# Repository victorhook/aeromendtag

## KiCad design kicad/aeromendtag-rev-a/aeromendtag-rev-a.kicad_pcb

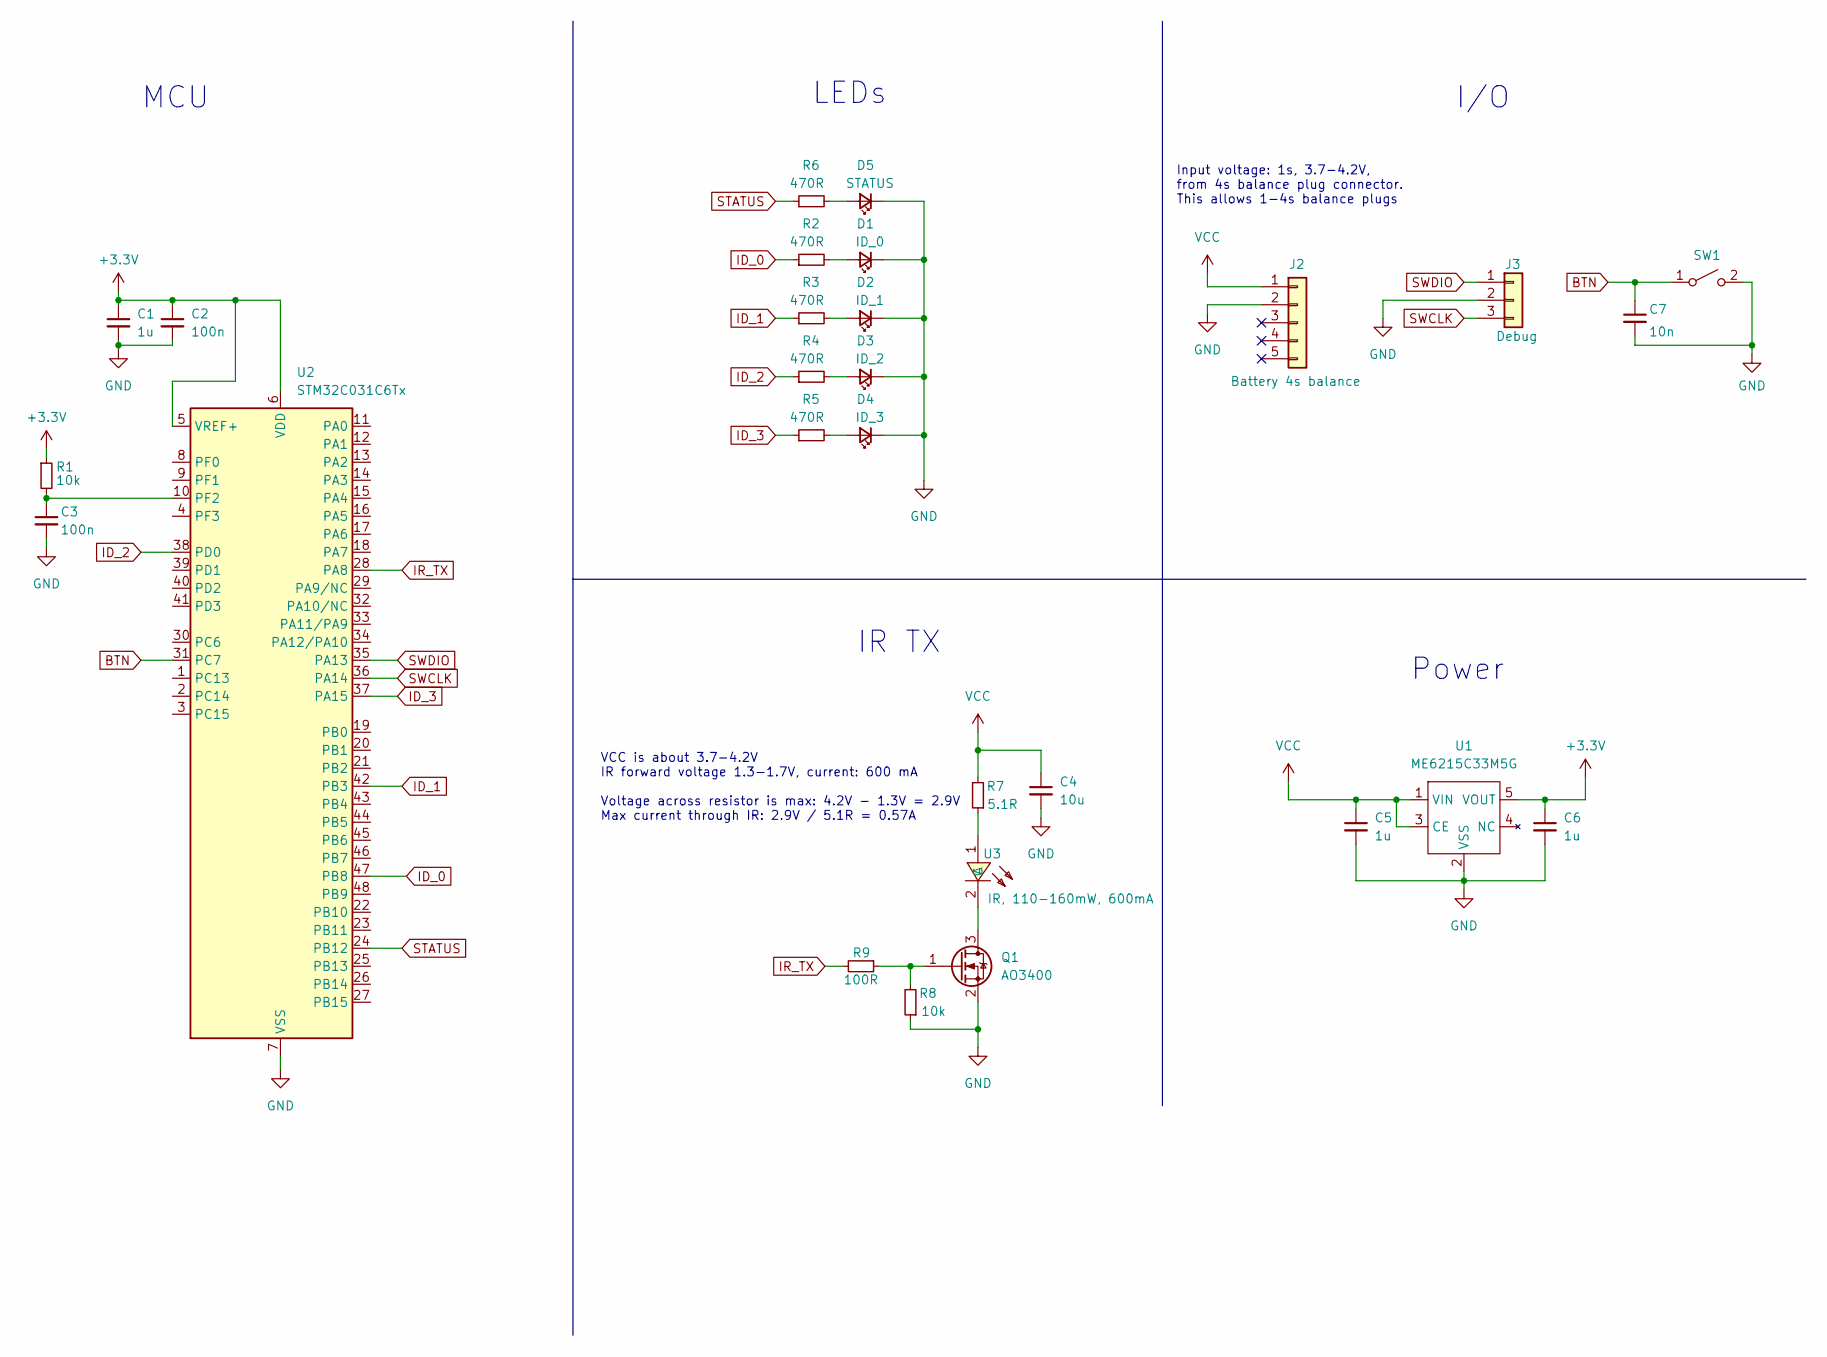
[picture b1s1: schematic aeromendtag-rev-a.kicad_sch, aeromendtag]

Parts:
C1, C5, C6: 1u; C_0402_1005Metric
C2, C3: 100n; C_0402_1005Metric
C4: 10u; C_0603_1608Metric
C7: 10n; C_0402_1005Metric
D1: ID_0; LED_0603_1608Metric
D2: ID_1; LED_0603_1608Metric
D3: ID_2; LED_0603_1608Metric
D4: ID_3; LED_0603_1608Metric
D5: STATUS; LED_0603_1608Metric
J2: Battery 4s balance; PinSocket_1x05_P2.54mm_Vertical
J3: Debug; PinHeader_1x03_P1.27mm_Vertical
Q1: AO3400; SOT-23; MPN C122850
R1, R8: 10k; R_0402_1005Metric
R2, R3, R4, R5, R6: 470R; R_0402_1005Metric
R7: 5.1R; R_2512_6332Metric; MPN C105134
R9: 100R; R_0402_1005Metric
SW1: SW_SPST; SW-SMD_L4.0-W2.9-LS5.0
U1: ME6215C33M5G; SOT-23-5; MPN C84119
U2: STM32C031C6Tx; LQFP-48_7x7mm_P0.5mm; MPN C5456218
U3: IR, 110-160mW, 600mA; SENSOR-SMD_L3.9-W3.9-FD; MPN C5205232; LCSC Part C5205232

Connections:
+3.3V: C1.1, C2.1, C6.1, R1.1, U1.5 (VOUT), U2.5 (VREF+), U2.6 (VDD)
BTN: C7.1, SW1.1 (A), U2.31 (PC7)
GND: C1.2, C2.2, C3.2, C4.2, C5.2, C6.2, C7.2, D1.1 (K), D2.1 (K), D3.1 (K), D4.1 (K), D5.1 (K), J2.2, J3.2, Q1.2 (S), R8.1, SW1.2 (B), U1.2 (VSS), U2.7 (VSS)
ID_0: R2.1, U2.47 (PB8)
ID_1: R3.1, U2.42 (PB3)
ID_2: R4.1, U2.38 (PD0)
ID_3: R5.1, U2.37 (PA15)
IR_TX: R9.2, U2.28 (PA8)
unnamed: D1.2 (A), R2.2
unnamed: D2.2 (A), R3.2
unnamed: D3.2 (A), R4.2
unnamed: D4.2 (A), R5.2
unnamed: D5.2 (A), R6.2
unnamed: Q1.3 (D), U3.2 (C)
unnamed: Q1.1 (G), R8.2, R9.1
unnamed: C3.1, R1.2, U2.10 (PF2)
unnamed: R7.1, U3.1 (A)
STATUS: R6.1, U2.24 (PB12)
SWCLK: J3.3, U2.36 (PA14)
SWDIO: J3.1, U2.35 (PA13)
VCC: C4.1, C5.1, J2.1, R7.2, U1.1 (VIN), U1.3 (CE)

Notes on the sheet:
MCU
VCC is about 3.7-4.2V IR forward voltage 1.3-1.7V, current: 600 mA Voltage across resistor is max: 4.2V - 1.3V = 2.9V Max current through IR: 2.9V / 5.1R = 0.57A
LEDs
IR TX
Power
I/O
Input voltage: 1s, 3.7-4.2V, from 4s balance plug connector. This allows 1-4s balance plugs

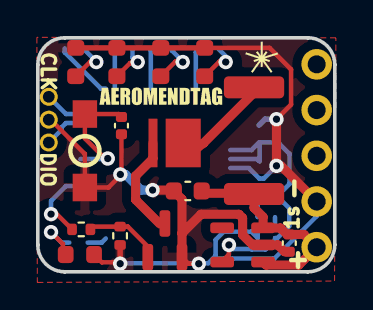
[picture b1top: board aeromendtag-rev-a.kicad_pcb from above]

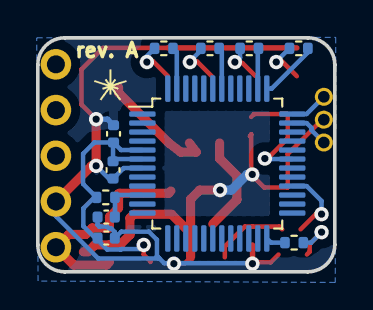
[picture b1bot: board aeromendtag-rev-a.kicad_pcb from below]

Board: 2 copper layers, 16.5 x 13.0 mm, 28 parts (12 on the bottom side), 21 nets.

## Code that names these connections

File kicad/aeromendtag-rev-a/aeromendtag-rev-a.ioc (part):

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Mcu.Name=STM32C031C(4-6)Tx
Mcu.Package=LQFP48
Mcu.UserName=STM32C031C6Tx
PA13.Mode=Serial_Wire
PA13.Signal=DEBUG_SWDIO
PA14-BOOT0.Mode=Serial_Wire
PA14-BOOT0.Signal=DEBUG_SWCLK
PA15.GPIOParameters=GPIO_Label
PA15.GPIO_Label=ID_3
PA15.Signal=GPIO_Output
PA8.Signal=S_TIM1_CH1
PB12.GPIOParameters=GPIO_Label
PB12.GPIO_Label=STATUS
PB12.Signal=GPIO_Output
PB3.GPIOParameters=GPIO_Label
PB3.GPIO_Label=ID_1
PB3.Signal=GPIO_Output
PB8.GPIOParameters=GPIO_Label
PB8.GPIO_Label=ID_0
PB8.Signal=GPIO_Output
PC7.GPIOParameters=GPIO_PuPd
PC7.GPIO_PuPd=GPIO_PULLUP
PC7.Signal=GPIO_Input
PD0.GPIOParameters=GPIO_Label
PD0.GPIO_Label=ID_2
PD0.Signal=GPIO_Output
RCC.HSE_VALUE=8000000
RCC.SYSCLKFreq_VALUE=12000000
board=custom
